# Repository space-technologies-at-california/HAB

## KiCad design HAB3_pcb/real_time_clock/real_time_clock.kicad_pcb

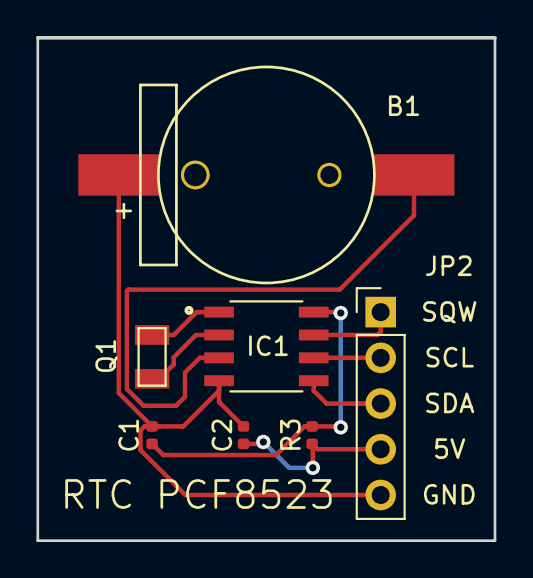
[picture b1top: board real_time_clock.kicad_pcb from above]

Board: 4 copper layers, 25.4 x 27.9 mm, 7 parts (0 on the bottom side), 9 nets.

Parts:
B1: CR1220; S8411-45R
C1, C2: 10uF; C_0402_1005Metric
IC1: RTC_PCF8523T; SOIC127P600X175-8N
JP2: HEADER-1X576MIL; PinHeader_1x05_P2.54mm_Vertical
Q1: 32.768KHz; XTAL320X150X90
R3: 1K; R_0402_1005Metric

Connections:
/SCL: IC1.6, JP2.2
/SDA: IC1.5, JP2.3
/SQW: IC1.7, JP2.1
GND: B1.1, C1.2, C2.2, IC1.4, JP2.5
unnamed: B1.2, IC1.3
unnamed: C1.1, IC1.8, R3.2
unnamed: IC1.1, Q1.1
unnamed: IC1.2, Q1.2
VCC: C2.1, JP2.4, R3.1

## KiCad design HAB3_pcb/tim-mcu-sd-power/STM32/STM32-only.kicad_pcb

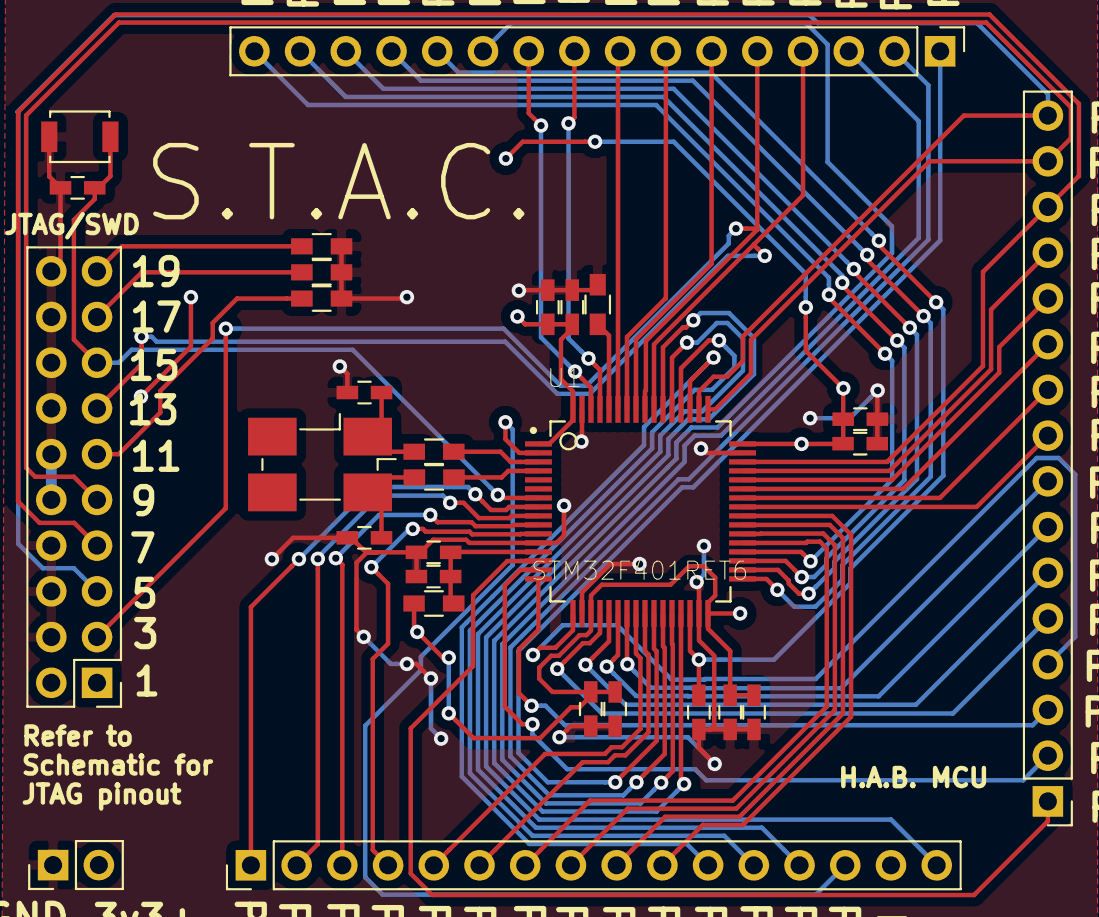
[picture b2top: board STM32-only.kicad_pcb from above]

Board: 4 copper layers, 29 parts (0 on the bottom side), 59 nets.

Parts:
0k1: R1; R_0603_HandSoldering
0k2: R2; R_0603_HandSoldering
1uF1: C6; C_0603_HandSoldering
1uF2: C14; C_0603_HandSoldering
1uF3: C8; C_0603_HandSoldering
1uF4: C12; C_0603_HandSoldering
1uF5: C10; C_0603_HandSoldering
4.7uF1: C21; C_0603_HandSoldering
10k1: R6; R_0603_HandSoldering
10k2: R7; R_0603_HandSoldering
10k3: R8; R_0603_HandSoldering
10k4: R5; R_0603_HandSoldering
10nF1: C7; C_0603_HandSoldering
22uH1: L1; L_0603_HandSoldering
100nF1: C5; C_0603_HandSoldering
100nF2: C15; C_0603_HandSoldering
100nF3: C9; C_0603_HandSoldering
100nF4: C13; C_0603_HandSoldering
100nF5: C11; C_0603_HandSoldering
C1, C2: 4.3pF; C_0603_HandSoldering
J1: Conn_ARM_JTAG_SWD_20; Pin_Header_Straight_2x10_Pitch2.54mm
J3, J4, J5: Conn_01x16_Male; Pin_Header_Straight_1x16_Pitch2.54mm
J6: Conn_01x02_Male; Pin_Header_Straight_1x02_Pitch2.54mm
SW1: SW_DPST_x2; SW_SPST_B3U-1000P
U1: STM32F401RET6; QFP50P1200X1200X160-64N
Y1: 32.768MHz; Crystal_SMD_0603-4pin_6.0x3.5mm_HandSoldering

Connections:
+3.3VA: 1uF1.2, 10nF1.2, 22uH1.1, U1.13
+3V3: 1uF2.2, 1uF3.2, 1uF4.2, 1uF5.2, 22uH1.2, 100nF2.2, 100nF3.2, 100nF4.2, 100nF5.2, J1.1, J1.2, J6.2, U1.1, U1.19, U1.32, U1.48, U1.64
GND: 1uF1.1, 1uF2.1, 1uF3.1, 1uF4.1, 1uF5.1, 4.7uF1.1, 10k1.1, 10k2.1, 10k3.1, 10k4.2, 10nF1.1, 100nF1.2, 100nF2.1, 100nF3.1, 100nF4.1, 100nF5.1, C1.2, C2.2, J1.4, J1.6, J1.8, J1.10, J1.12, J1.14, J1.16, J1.18, J1.20, J6.1, SW1.1, U1.12, U1.18, U1.31, U1.47, U1.63
unnamed: 0k1.1, U1.3
unnamed: 0k1.2, C1.1, Y1.1
unnamed: 0k2.1, U1.4
unnamed: 0k2.2, C2.1, Y1.4
unnamed: 10k1.2, J1.11
unnamed: 10k2.2, J1.19
unnamed: 10k3.2, J1.17
unnamed: 10k4.1, U1.60
PA0: J3.1, U1.14
PA1: J3.2, U1.15
PA2: J3.3, U1.16
PA3: J3.4, U1.17
PA4: J3.5, U1.20
PA5: J3.6, U1.21
PA6: J3.7, U1.22
PA7: J3.8, U1.23
PA8: J3.9, U1.41
PA9: J3.10, U1.42
PA10: J3.11, U1.43
PA11: J3.12, U1.44
PA12: J3.13, U1.45
PA13: J1.7, J3.14, U1.46
PA14: J1.9, J3.15, U1.49
PA15: J1.5, J3.16, U1.50
PB0: J4.1, U1.26
PB1: J4.2, U1.27
PB2: J4.3, U1.28
PB3: J1.13, J4.4, U1.55
PB4: J1.3, J4.5, U1.56
PB5: J4.6, U1.57
PB6: J4.7, U1.58
PB7: J4.8, U1.59
PB8: J4.9, U1.61
PB9: J4.10, U1.62
PB10: J4.11, U1.29
PB11: 4.7uF1.2, J4.12, U1.30
PB12: J4.13, U1.33
PB13: J4.14, U1.34
PB14: J4.15, U1.35
PB15: J4.16, U1.36
PC0: J5.1, U1.8
PC1: J5.2, U1.9
PC2: J5.3, U1.10
PC3: J5.4, U1.11
PC4: J5.5, U1.24
PC5: J5.6, U1.25
PC6: J5.7, U1.37
PC7: J5.8, U1.38
PC8: J5.9, U1.39
PC9: J5.10, U1.40
PC10: J5.11, U1.51
PC11: J5.12, U1.52
PC12: J5.13, U1.53
PC13: J5.14, U1.2
PD2: J5.16, U1.54
RST: 100nF1.1, J1.15, SW1.2, U1.7

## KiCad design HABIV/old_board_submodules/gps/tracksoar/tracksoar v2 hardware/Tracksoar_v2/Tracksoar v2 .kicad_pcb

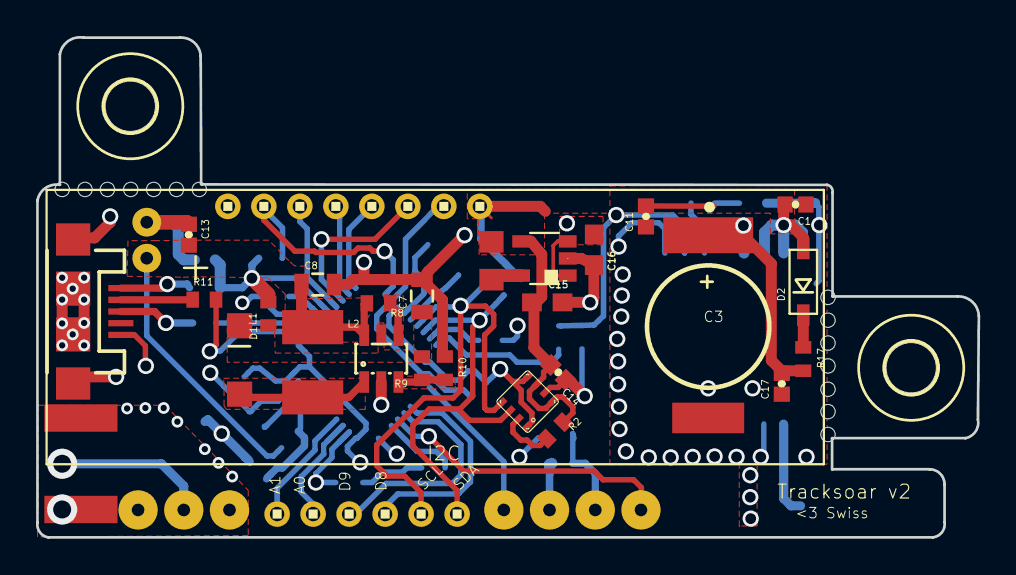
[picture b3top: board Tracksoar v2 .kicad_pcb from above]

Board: 4 copper layers, 52.3 x 27.8 mm, 73 parts (0 on the bottom side), 47 nets.

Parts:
@HOLE0, @HOLE1, @HOLE2, @HOLE3, @HOLE4, @HOLE5, @HOLE6, @HOLE7, @HOLE8, @HOLE9, @HOLE10, @HOLE11, @HOLE12, @HOLE13: (no value)
C1, C2, C4, C6, C9, C10, C11, C13, C14, C17: .1uf; 0402-CAP
C3: GPS BACKUP; DSK-3R3H204T614-H2L
C5, C12: 1uf; 0402-CAP
C7: 22uf; 0805
C8: 10uf; 0805
C15, C16: 10uF; 0603
D1: MBR120VLSFT1; SOD123
D2: SD101CW; SOD-123
F1: PTC0603; 0603
FRAME1: FRAME-LETTER; CREATIVE_COMMONS
FTDI1: 1X8
GPS-ANT1: 1.575GHz; ANT-GPS-2X7MM
GPSLOCK1: LEDCHIP-LED0603; CHIP-LED0603
H1, H2: MOUNT-HOLE2.8; 2,8
IC1: BME280
J1: battery; JST-2-PTH
J$1: SMA_EDGE; SMA-EDGE
JP1: USB-MICROB
L1: BLM15H; 0402
L2: 2.2uh; L1812
LT3426: LT3426; SOT23-6
PTT1: LEDCHIP-LED0603; CHIP-LED0603
R1, R6: 1k; R0402
R2, R3, R7, R15: 4.7k; R0402
R4, R11: 22ohm; R0402
R5, R12, R13, R14, R16: 10k; R0402
R8: 1m; R0402
R9: 95.3k; R0402
R10: 30.9k; R0402
R17: 330; R0402
U$1: UBLOX_MAX
U$2: RADIOMETRIX-HX1
U$3: 1X6
U$4: ATMEGA32U4; QFN-44-NOPAD
U$5: PAM2305; DBV_R-PDSO-G5
U$6: 4.7uH; RESC0805_N
U$7: INDUCTOR_0402_N; RESC0402_N
Y1: 16MHZ; RESONATOR-SMD

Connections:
/3V: C15.1, D2.A, FTDI1.1, IC1.6, IC1.8, R2.1, R3.1, R7.1, U$1.7_VCC_IO, U$1.8_VCC, U$1.9_V_RESET, U$5.4, U$6.1
/A0: U$3.2, U$4.36
/A1: U$3.1, U$4.37
/D3: U$2.TXD, U$4.30
/D4: U$2.EN, U$4.25
/D8: U$3.4, U$4.28
/D9: U$3.3, U$4.29
/D+: R4.2, U$4.4
/D-: R11.2, U$4.3
/HWB: R12.2, U$4.33
/LED: R6.2, U$4.31
/MISO: FTDI1.4, U$4.11
/MOSI: FTDI1.5, U$4.10
/PPS: R1.1, U$1.4_TIMEPULSE
/RFGND: J$1.GND@0, J$1.GND@1, J$1.GND@2, J$1.GND@3, U$2.RFGND, U$2.RFGND2, U$7.2
/RX: R16.1, U$4.20
/RX1: R16.2, U$1.2_TXD1
/SCK: FTDI1.3, U$4.9
/SCL: IC1.4, R7.2, U$3.5, U$4.18
/SDA: IC1.3, R3.2, U$3.6, U$4.19
/SS: FTDI1.6, U$4.8
/TX: R15.2, U$4.21
/TX1: R14.1, R15.1, U$1.3_RXD1
/VBACKUP: C3.1, C17.2, R17.2, U$1.6_V_BCKP
/VIN: C8.1, C13.2, J1.2, L2.1, LT3426.6, R8.2, R13.1
/VSENSE: C6.2, R13.2, U$4.41
/~RESET: FTDI1.7, R5.1, U$4.13
GND: C1.1, C2.1, C3.2, C4.1, C5.1, C6.1, C7.2, C8.2, C9.1, C10.1, C11.1, C12.1, C13.1, C14.1, C15.2, C16.2, C17.1, FTDI1.8, GPSLOCK1.C, IC1.1, IC1.5, IC1.7, J1.1, JP1.GND, JP1.MT1, JP1.MT2, LT3426.2, PTT1.C, R10.1, R12.1, R14.2, U$1.1_GND, U$1.10_GND, U$1.12_GND, U$2.0V, U$4.5, U$4.15, U$4.23, U$4.35, U$4.43, U$5.2, U$7.1, Y1.2
unnamed: C5.2, U$4.6
unnamed: C7.1, D1.C, L1.1, LT3426.5, R9.2
unnamed: C12.2, U$4.42
unnamed: D1.A, L2.2, LT3426.1
unnamed: D2.C, R17.1
unnamed: F1.1, JP1.VBUS
unnamed: GPS-ANT1.1, U$1.11_RF_IN
unnamed: GPSLOCK1.A, R1.2
unnamed: IC1.2, R2.2
unnamed: J$1.SIG, U$2.RFOUT
unnamed: JP1.D+, R4.1
unnamed: JP1.D-, R11.1
unnamed: LT3426.3, R9.1, R10.2
unnamed: LT3426.4, R8.1
unnamed: PTT1.A, R6.1
unnamed: U$4.16, Y1.3
unnamed: U$4.17, Y1.1
unnamed: U$5.5, U$6.2
VCC: C2.2, C4.2, C9.2, C10.2, C16.1, F1.2, FTDI1.2, L1.2, R5.2, U$2.VCC, U$4.2, U$4.7, U$4.14, U$4.24, U$4.34, U$4.44, U$5.1, U$5.3

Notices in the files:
parts and their libraries:
https://creativecommons.org/licenses/by-sa/4.0
Released under the Creative Commons Attribution Share-Alike 4.0 License
